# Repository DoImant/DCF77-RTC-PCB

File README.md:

# Circuit board for a DCF77 radio clock.

This project is a circuit board for the components of a DCF77 radio clock.
The components (display, RTC module and DFC77 receiver can be plugged in directly or connected by cable. 
The buttons for controlling the date display and the backlight must be connected by cable.

## The PCB

## Software

The software and a breadboard setup are presented here: https://github.com/DoImant/Arduino-DCF77-RTC

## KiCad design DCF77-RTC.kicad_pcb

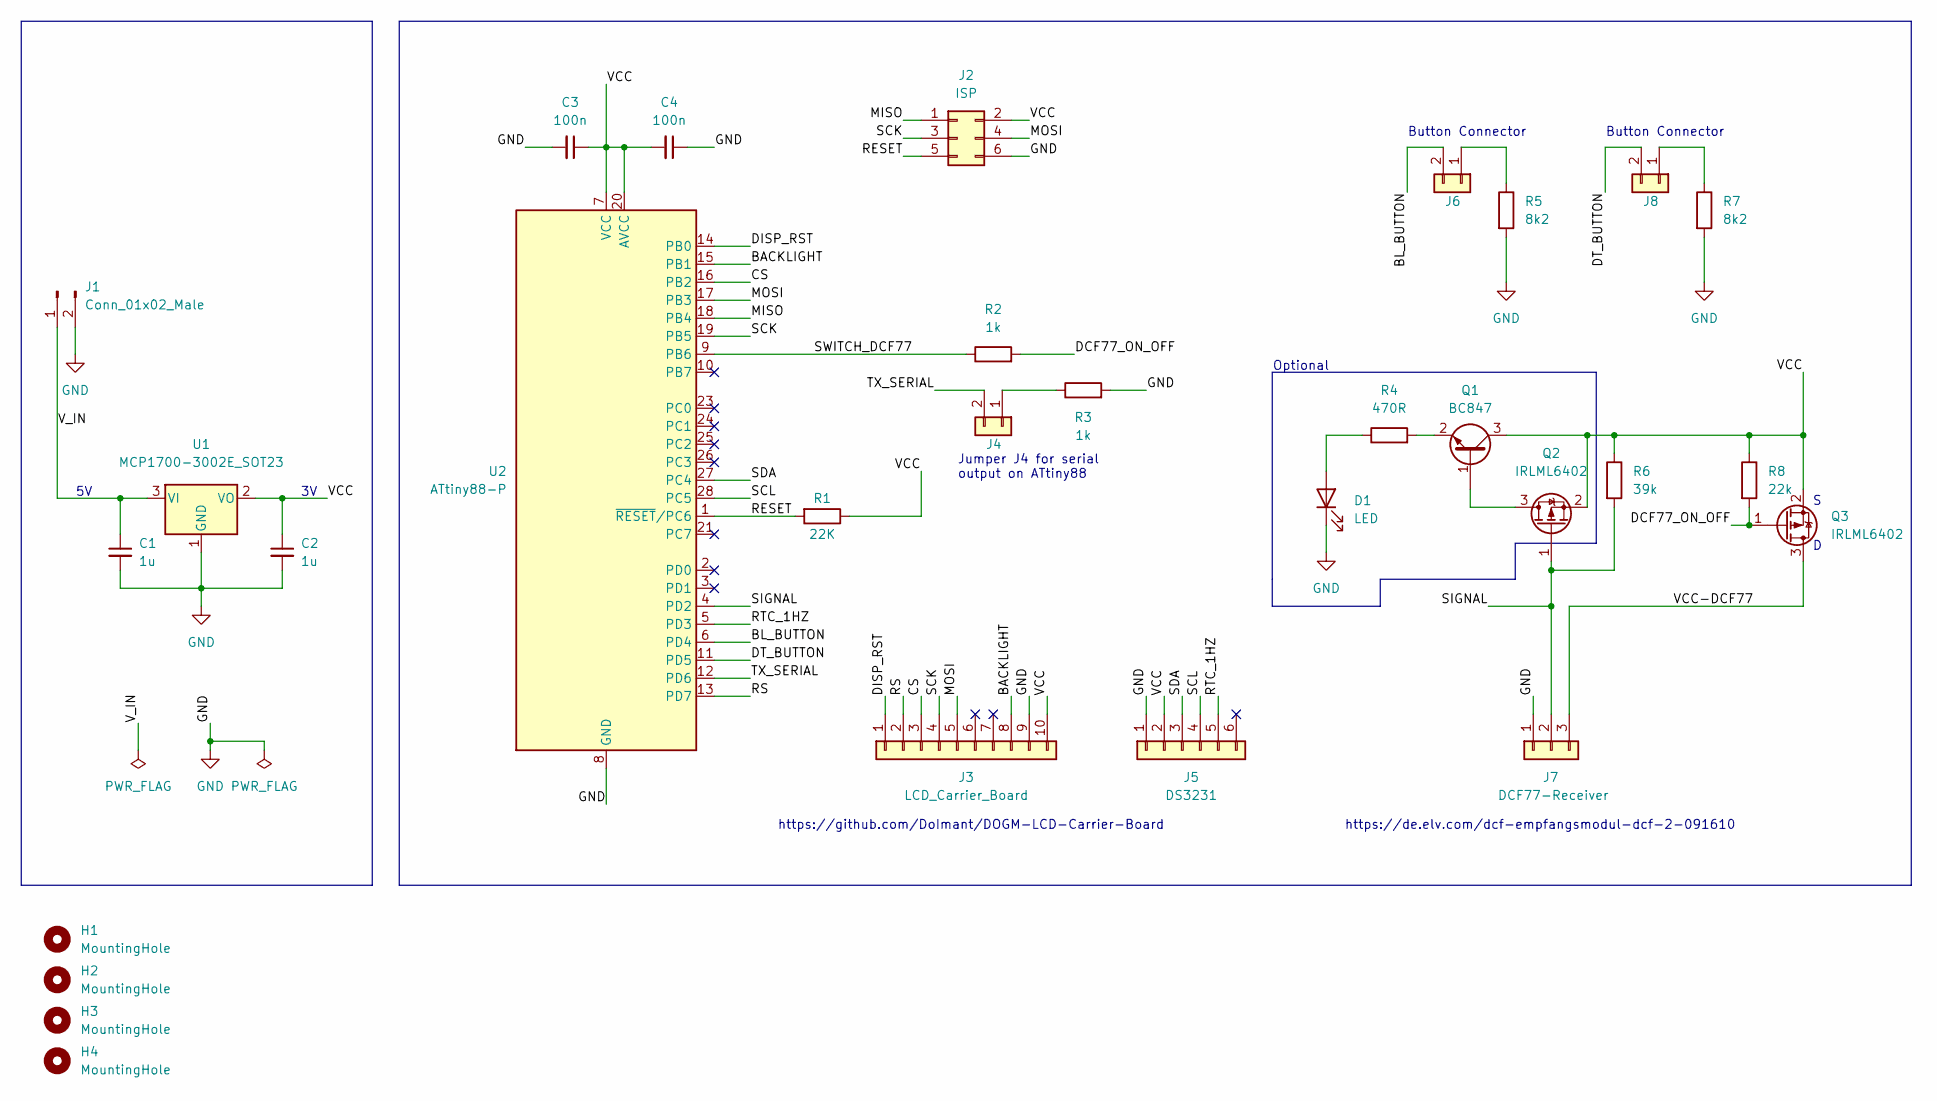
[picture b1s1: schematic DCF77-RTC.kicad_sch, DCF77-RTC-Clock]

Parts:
C1, C2: 1u; C_1206_3216Metric_Pad1.33x1.80mm_HandSolder
C3, C4: 100n; C_0805_2012Metric_Pad1.18x1.45mm_HandSolder
D1: LED; LED_1206_3216Metric_Pad1.42x1.75mm_HandSolder
H1, H2, H3, H4: MountingHole; MountingHole_3mm
J1: Conn_01x02_Male; JST_XH_B2B-XH-A_1x02_P2.50mm_Vertical
J2: ISP; IDC-Header_2x03_P2.54mm_Vertical
J3: LCD_Carrier_Board; PinSocket_1x10_P2.54mm_Vertical
J4, J6, J8: Conn_01x02; PinHeader_1x02_P2.54mm_Vertical
J5: DS3231; PinSocket_1x06_P2.54mm_Vertical
J7: DCF77-Receiver; PinSocket_1x03_P2.54mm_Vertical
Q1: BC847; SOT-23
Q2, Q3: IRLML6402; SOT-23
R1: 22K; R_1206_3216Metric_Pad1.30x1.75mm_HandSolder
R2, R3: 1k; R_1206_3216Metric_Pad1.30x1.75mm_HandSolder
R4: 470R; R_1206_3216Metric_Pad1.30x1.75mm_HandSolder
R5, R7: 8k2; R_1206_3216Metric_Pad1.30x1.75mm_HandSolder
R6: 39k; R_1206_3216Metric_Pad1.30x1.75mm_HandSolder
R8: 22k; R_1206_3216Metric_Pad1.30x1.75mm_HandSolder
U1: MCP1700-3002E_SOT23; SOT-23
U2: ATtiny88-P; DIP-28_W7.62mm_Socket_LongPads

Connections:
/BACKLIGHT: J3.8, U2.15 (PB1)
/BL_BUTTON: J6.2, U2.6 (PD4)
/CS: J3.3, U2.16 (PB2)
/DCF77_ON_OFF: Q3.1 (G), R2.2, R8.2
/DISP_RST: J3.1, U2.14 (PB0)
/DT_BUTTON: J8.2, U2.11 (PD5)
/MISO: J2.1, U2.18 (PB4)
/MOSI: J2.4, J3.5, U2.17 (PB3)
/RESET: J2.5, R1.2, U2.1 (~RESET/PC6)
/RS: J3.2, U2.13 (PD7)
/RTC_1HZ: J5.5, U2.5 (PD3)
/SCK: J2.3, J3.4, U2.19 (PB5)
/SCL: J5.4, U2.28 (PC5)
/SDA: J5.3, U2.27 (PC4)
/SIGNAL: J7.2, Q2.1 (G), R6.2, U2.4 (PD2)
/SWITCH_DCF77: R2.1, U2.9 (PB6)
/TX_SERIAL: J4.2, U2.12 (PD6)
/VCC: C2.1, C3.1, C4.2, J2.2, J3.10, J5.2, Q1.3 (C), Q2.2 (S), Q3.2 (S), R1.1, R6.1, R8.1, U1.2 (VO), U2.7 (VCC), U2.20 (AVCC)
/VCC-DCF77: J7.3, Q3.3 (D)
/V_IN: C1.1, J1.1, U1.3 (VI)
GND: C1.2, C2.2, C3.2, C4.1, D1.1 (K), J1.2, J2.6, J3.9, J5.1, J7.1, R3.2, R5.2, R7.2, U1.1 (GND), U2.8 (GND), U2.22 (GND)
unnamed: D1.2 (A), R4.1
unnamed: J4.1, R3.1
unnamed: J6.1, R5.1
unnamed: J8.1, R7.1
unnamed: Q1.1 (B), Q2.3 (D)
unnamed: Q1.2 (E), R4.2

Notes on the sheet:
Button Connector
Optional
https://github.com/DoImant/DOGM-LCD-Carrier-Board
Jumper J4 for serial output on ATtiny88
https://de.elv.com/dcf-empfangsmodul-dcf-2-091610

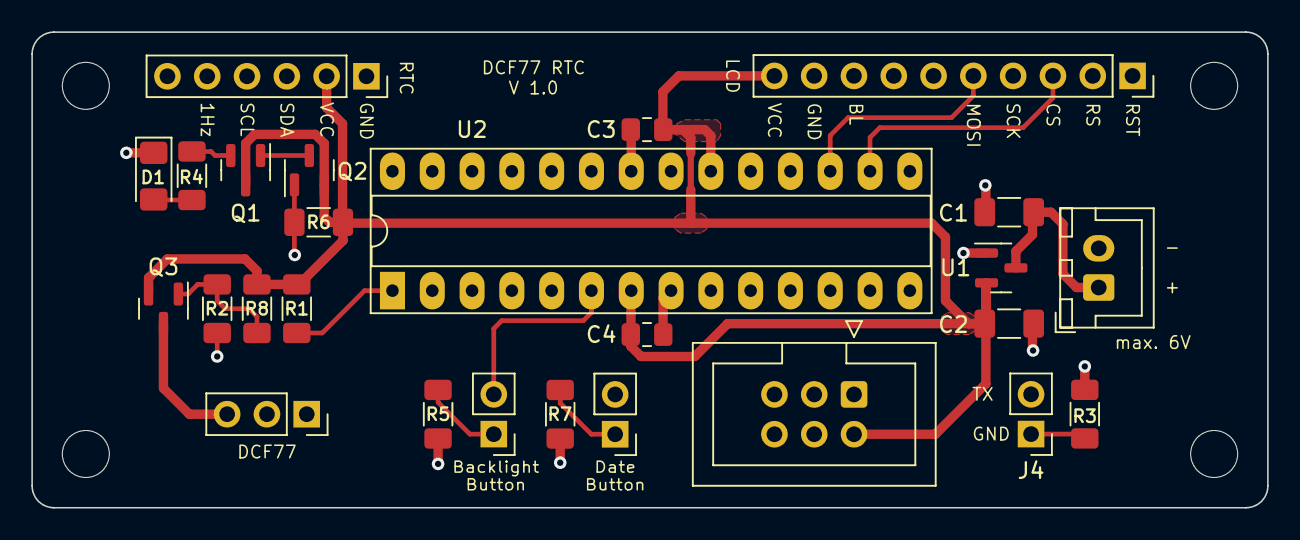
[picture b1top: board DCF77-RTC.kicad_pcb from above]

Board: 4 copper layers, 78.9 x 30.4 mm, 30 parts (0 on the bottom side), 27 nets.

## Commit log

2022-06-10 Corrected README.md
2022-06-12 one file deleted
